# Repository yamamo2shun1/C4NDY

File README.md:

# C4NDY KeyVLM / STK

## Documentation
- [See the official documentation on https://yamamo2shun1.github.io/C4NDY/](https://yamamo2shun1.github.io/C4NDY/)

The docs are powered by [VitePress](https://vitepress.dev/). 

## Submodule
[TinyUSB](https://github.com/hathach/tinyusb) is included as a submodule in [STM32CubeIDE/C4NDY_KeyVLM](https://github.com/yamamo2shun1/C4NDY/tree/main/STM32CubeIDE/C4NDY_KeyVLM) and [STM32CubeIDE/C4NDY_STK](https://github.com/yamamo2shun1/C4NDY/tree/main/STM32CubeIDE/C4NDY_STK). Since the version of TinyUSB that we have confirmed to work is [0.17.0](https://github.com/hathach/tinyusb/releases/tag/0.17.0), please check out to the [commit](https://github.com/hathach/tinyusb/commit/5217cee5de4cd555018da90f9f1bcc87fb1c1d3a) with this tag.

## Maintainer
C4NDY is developed and maintained by Shunichi Yamamoto of Yamamoto Works Ltd.

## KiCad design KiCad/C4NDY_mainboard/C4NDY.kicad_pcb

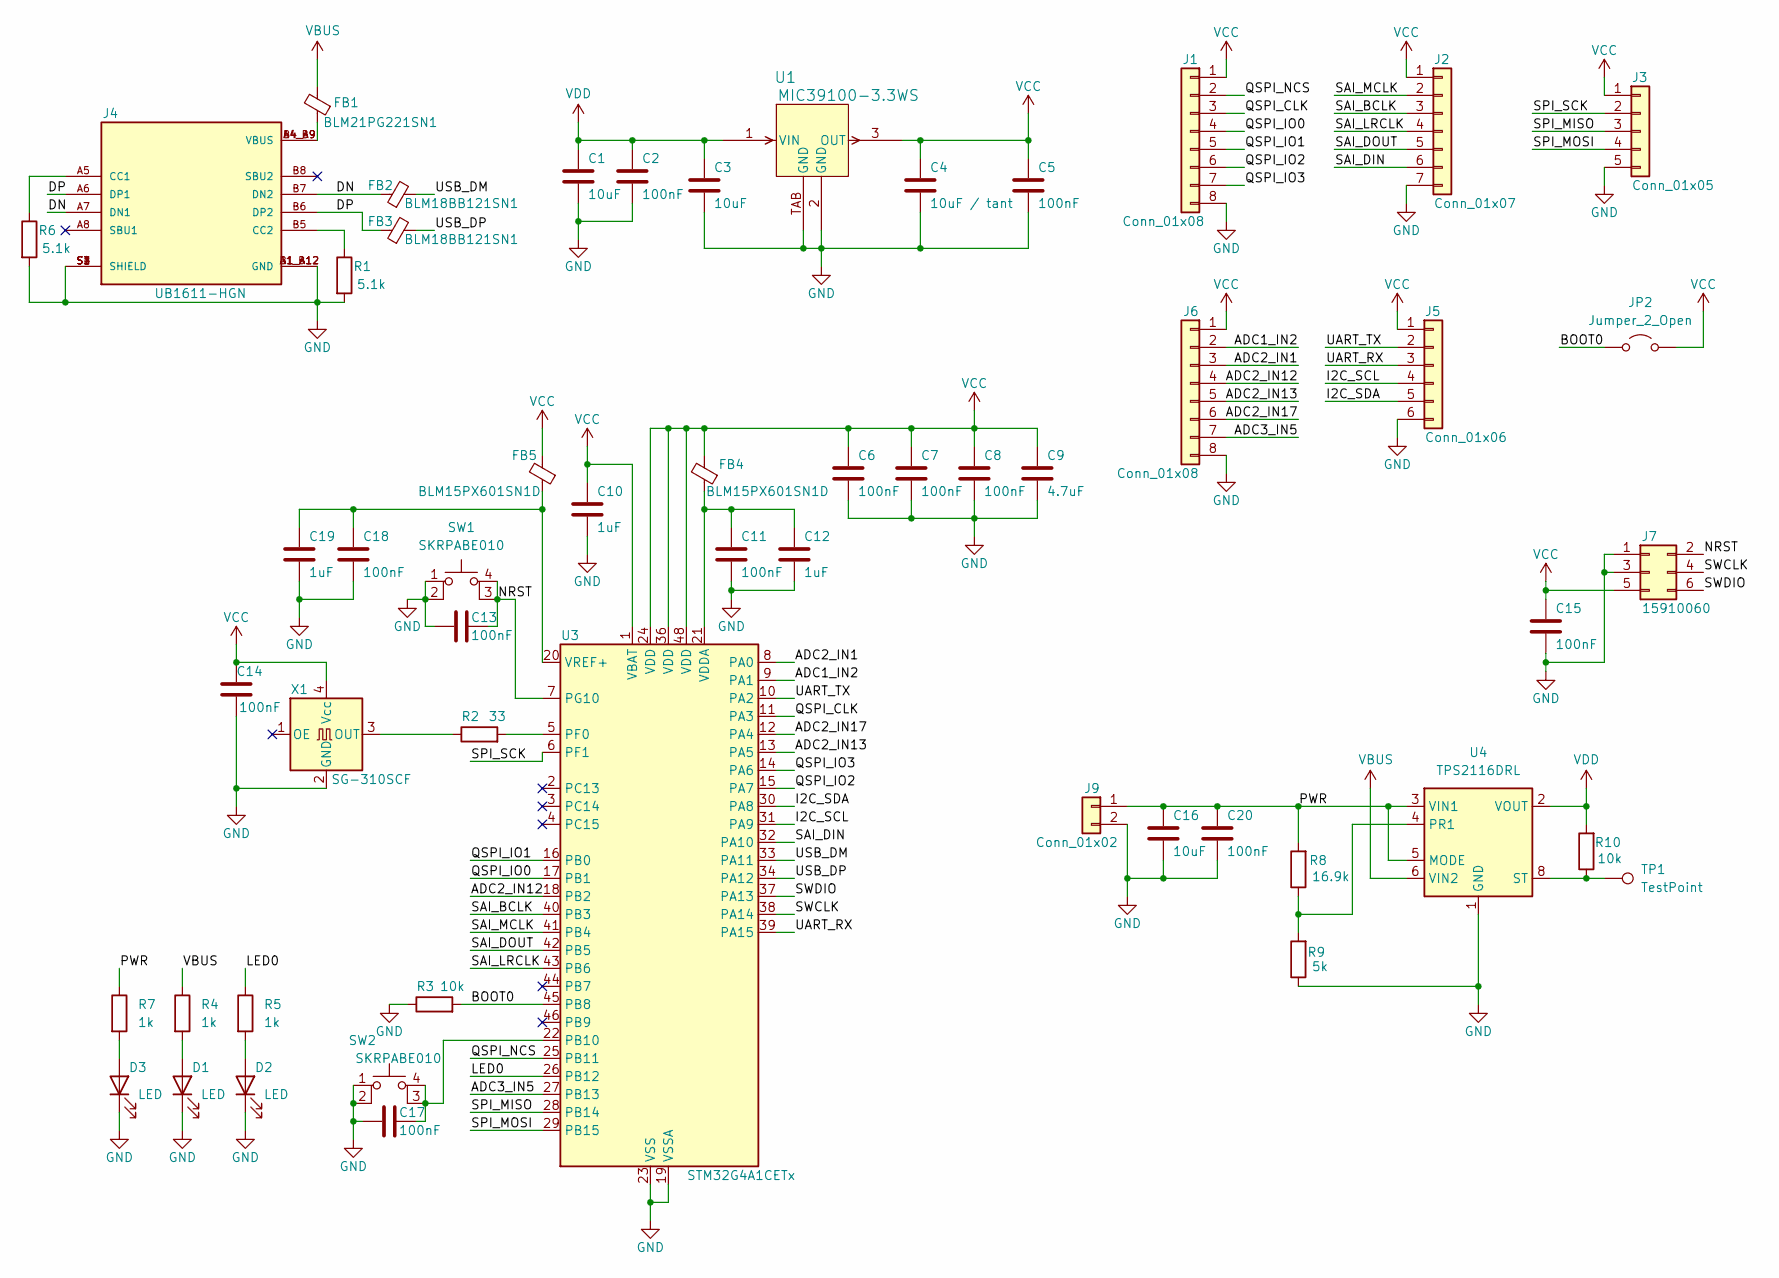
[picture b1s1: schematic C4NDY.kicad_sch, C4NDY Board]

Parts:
C1, C3, C16: 10uF; C_0603_1608Metric
C2, C5, C20: 100nF; C_0603_1608Metric
C4: 10uF / tant; CP_EIA-3528-12_Kemet-T
C6, C7, C8, C11, C13, C14, C15, C17, C18: 100nF; C_0402_1005Metric
C9: 4.7uF; C_0603_1608Metric
C10, C12, C19: 1uF; C_0402_1005Metric
D1, D2, D3: LED; LED_0603_1608Metric
FB1: BLM21PG221SN1; L_0805_2012Metric
FB2, FB3: BLM18BB121SN1; L_0603_1608Metric
FB4, FB5: BLM15PX601SN1D; L_0402_1005Metric
J1, J6: Conn_01x08; PinHeader_1x08_P2.54mm_Vertical
J2: Conn_01x07; PinHeader_1x07_P2.54mm_Vertical
J3: Conn_01x05; PinHeader_1x05_P2.54mm_Vertical
J4: UB1611-HGN; Gangyuan_UB1611-HGN; PARTREV B
J5: Conn_01x06; PinHeader_1x06_P2.54mm_Vertical
J7: 15910060; Molex_15910060
J9: Conn_01x02; PinHeader_1x02_P2.54mm_Vertical
JP2: Jumper_2_Open; SolderJumper-2_P1.3mm_Open_RoundedPad1.0x1.5mm
R1, R6: 5.1k; R_0402_1005Metric
R2: 33; R_0402_1005Metric
R3, R10: 10k; R_0402_1005Metric
R4, R5, R7: 1k; R_0402_1005Metric
R8: 16.9k; R_0402_1005Metric
R9: 5k; R_0402_1005Metric
SW1, SW2: SKRPABE010
TP1: TestPoint; TestPoint_THTPad_1.0x1.0mm_Drill0.5mm
U1: MIC39100-3.3WS; SOT-223_S_MCL
U3: STM32G4A1CETx; LQFP-48_7x7mm_P0.5mm
U4: TPS2116DRL; SOT-583-8
X1: SG-310SCF; Oscillator_SMD_SeikoEpson_SG8002CE-4Pin_3.2x2.5mm

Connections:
/ADC1_IN2: J6.2, U3.9 (PA1)
/ADC2_IN1: J6.3, U3.8 (PA0)
/ADC2_IN12: J6.4, U3.18 (PB2)
/ADC2_IN13: J6.5, U3.13 (PA5)
/ADC2_IN17: J6.6, U3.12 (PA4)
/ADC3_IN5: J6.7, U3.27 (PB13)
/BOOT0: JP2.1 (A), R3.2, U3.45 (PB8)
/DN: FB2.1, J4.A7 (DN1), J4.B7 (DN2)
/DP: FB3.1, J4.A6 (DP1), J4.B6 (DP2)
/I2C_SCL: J5.4, U3.31 (PA9)
/I2C_SDA: J5.5, U3.30 (PA8)
/LED0: R5.1, U3.26 (PB12)
/NRST: C13.1, J7.2, SW1.3 (K), SW1.4 (A), U3.7 (PG10)
/PWR: C16.1, C20.1, J9.1, R7.1, R8.2, U4.3 (VIN1), U4.5 (MODE)
/QSPI_CLK: J1.3, U3.11 (PA3)
/QSPI_IO0: J1.4, U3.17 (PB1)
/QSPI_IO1: J1.5, U3.16 (PB0)
/QSPI_IO2: J1.6, U3.15 (PA7)
/QSPI_IO3: J1.7, U3.14 (PA6)
/QSPI_NCS: J1.2, U3.25 (PB11)
/SAI_BCLK: J2.3, U3.40 (PB3)
/SAI_DIN: J2.6, U3.32 (PA10)
/SAI_DOUT: J2.5, U3.42 (PB5)
/SAI_LRCLK: J2.4, U3.43 (PB6)
/SAI_MCLK: J2.2, U3.41 (PB4)
/SPI_MISO: J3.3, U3.28 (PB14)
/SPI_MOSI: J3.4, U3.29 (PB15)
/SPI_SCK: J3.2, U3.6 (PF1)
/SWCLK: J7.4, U3.38 (PA14)
/SWDIO: J7.6, U3.37 (PA13)
/UART_RX: J5.3, U3.39 (PA15)
/UART_TX: J5.2, U3.10 (PA2)
/USB_DM: FB2.2, U3.33 (PA11)
/USB_DP: FB3.2, U3.34 (PA12)
GND: C1.2, C2.2, C3.2, C4.2, C5.2, C6.2, C7.2, C8.2, C9.2, C10.2, C11.2, C12.2, C13.2, C14.1, C15.2, C16.2, C17.2, C18.2, C19.2, C20.2, D1.1 (K), D2.1 (K), D3.1 (K), J1.8, J2.7, J3.5, J4.A1_B12 (GND), J4.B1_A12 (GND), J4.S1 (SHIELD), J4.S2 (SHIELD), J4.S3 (SHIELD), J4.S4 (SHIELD), J5.6, J6.8, J7.1, J7.3, J9.2, R1.2, R3.1, R6.2, R9.1, SW1.1, SW1.2, SW2.1, SW2.2, U1.2 (GND), U1.TAB (GND), U3.19 (VSSA), U3.23 (VSS), U3.35 (VSS), U3.47 (VSS), U4.1 (GND), X1.2 (GND)
unnamed: D1.2 (A), R4.2
unnamed: D2.2 (A), R5.2
unnamed: D3.2 (A), R7.2
unnamed: FB1.1, J4.A4_B9 (VBUS), J4.B4_A9 (VBUS)
unnamed: J4.A5 (CC1), R6.1
unnamed: J4.B5 (CC2), R1.1
unnamed: C17.1, SW2.3 (K), SW2.4 (A), U3.22 (PB10)
unnamed: R2.2, U3.5 (PF0)
unnamed: C11.1, C12.1, FB4.1, U3.21 (VDDA)
unnamed: C18.1, C19.1, FB5.1, U3.20 (VREF+)
unnamed: R8.1, R9.2, U4.4 (PR1)
unnamed: R10.1, TP1.1, U4.8 (ST)
unnamed: R2.1, X1.3 (OUT)
VBUS: FB1.2, R4.1, U4.6 (VIN2)
VCC: C4.1, C5.1, C6.1, C7.1, C8.1, C9.1, C10.1, C14.2, C15.1, FB4.2, FB5.2, J1.1, J2.1, J3.1, J5.1, J6.1, J7.5, JP2.2 (B), U1.3 (OUT), U3.1 (VBAT), U3.24 (VDD), U3.36 (VDD), U3.48 (VDD), X1.4 (Vcc)
VDD: C1.1, C2.1, C3.1, R10.2, U1.1 (VIN), U4.2 (VOUT), U4.7 (VOUT)

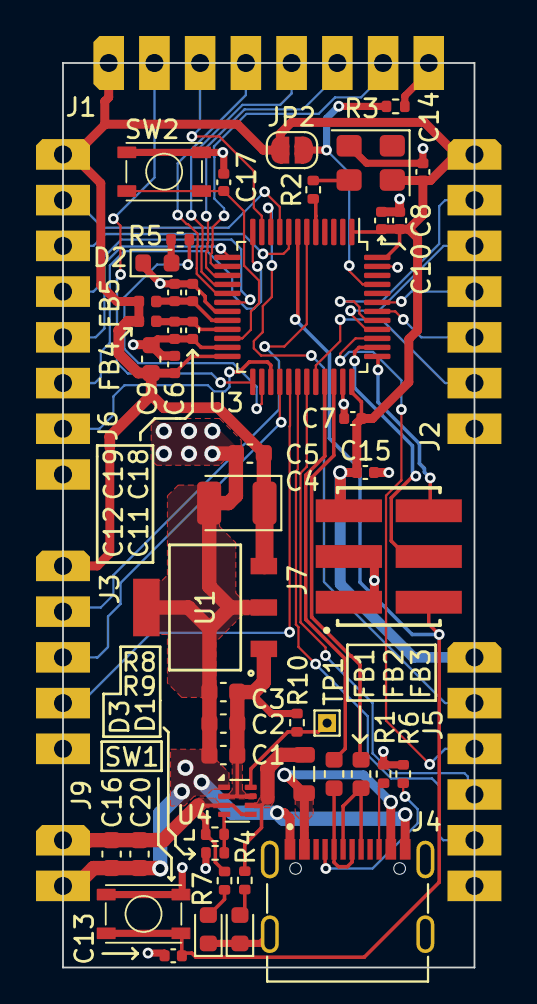
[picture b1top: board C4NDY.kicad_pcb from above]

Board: 2 copper layers, 22.9 x 50.2 mm, 54 parts (0 on the bottom side), 51 nets.

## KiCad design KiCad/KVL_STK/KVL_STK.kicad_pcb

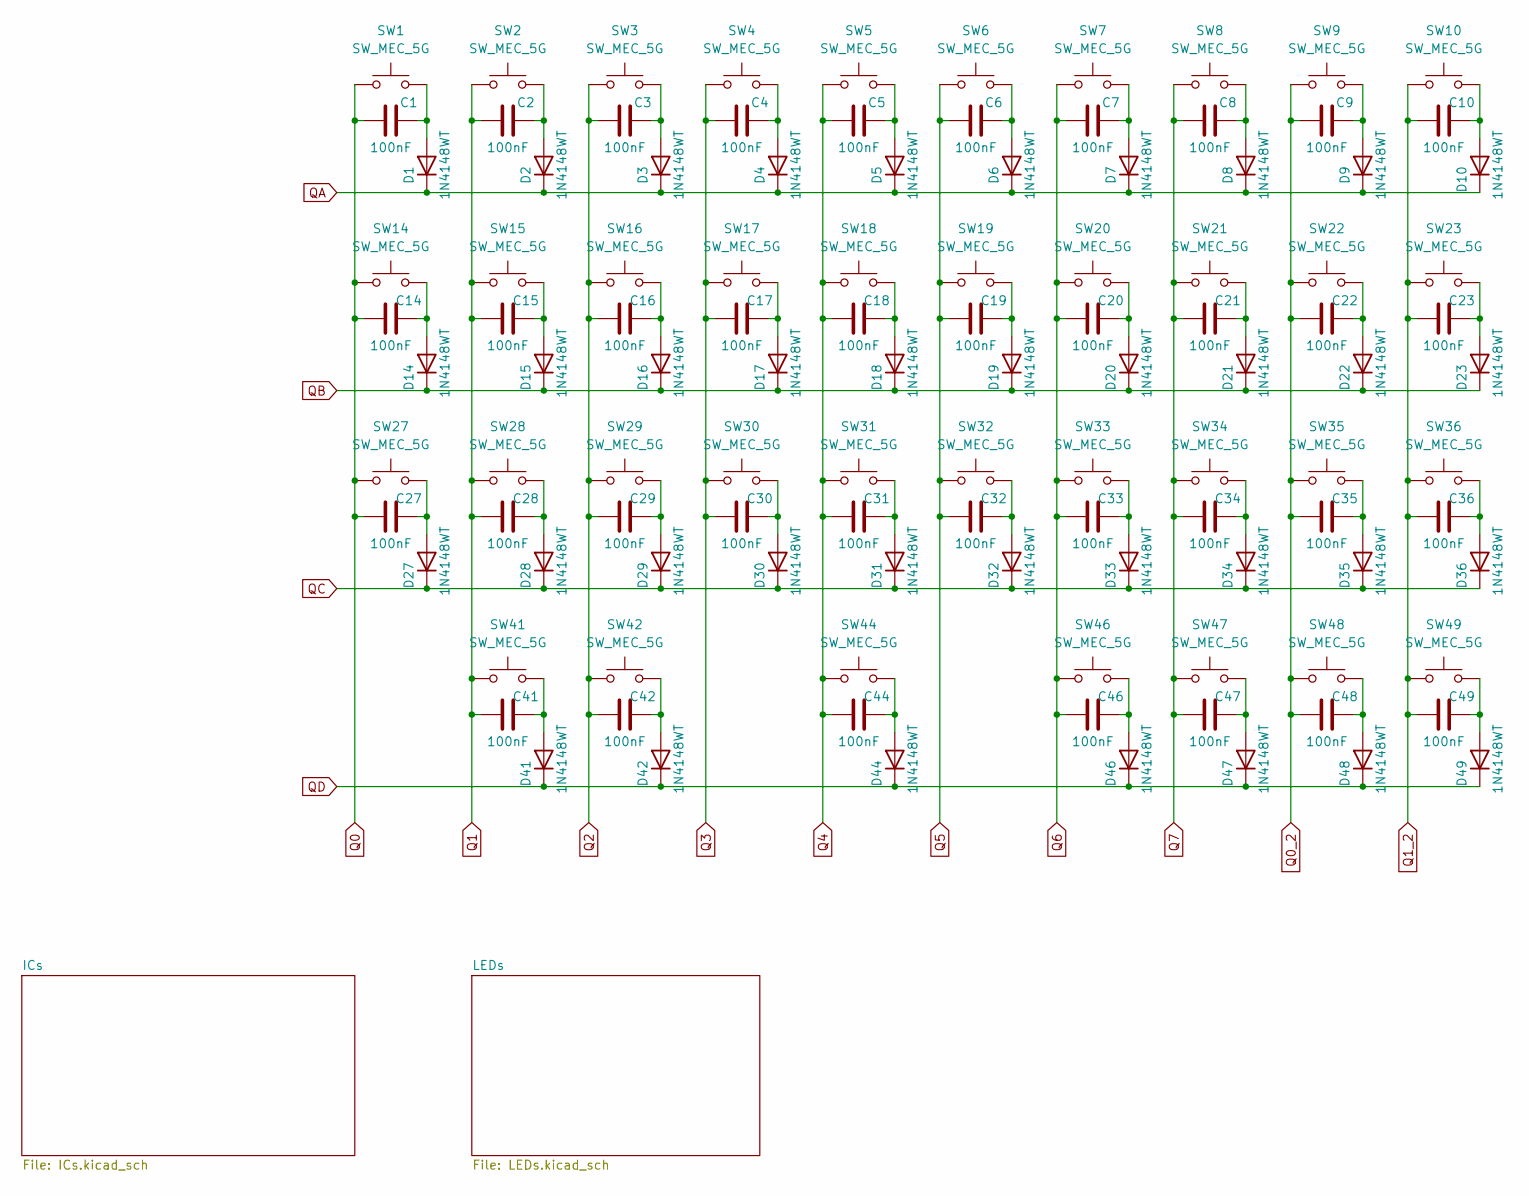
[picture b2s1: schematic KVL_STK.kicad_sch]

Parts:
C1, C2, C3, C4, C5, C6, C7, C8, C9, C10, C14, C15, C16, C17, C18, C19, C20, C21, C22, C23, C27, C28, C29, C30, C31, C32, C33, C34, C35, C36, C41, C42, C44, C46, C47, C48, C49: 100nF; C_0402_1005Metric
D1, D2, D3, D4, D5, D6, D7, D8, D9, D10, D14, D15, D16, D17, D18, D19, D20, D21, D22, D23, D27, D28, D29, D30, D31, D32, D33, D34, D35, D36, D41, D42, D44, D46, D47, D48, D49: 1N4148WT; D_SOD-523
SW1, SW2, SW3, SW4, SW5, SW6, SW7, SW8, SW9, SW10, SW14, SW15, SW16, SW17, SW18, SW19, SW20, SW21, SW22, SW23, SW27, SW28, SW29, SW30, SW31, SW32, SW33, SW34, SW35, SW36, SW41, SW42, SW44, SW46, SW47, SW48, SW49: SW_MEC_5G; Gateron_KS-27

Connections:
unnamed: C1.2, D1.2 (A), SW1.3 (B)
unnamed: C3.2, D3.2 (A), SW3.3 (B)
unnamed: C4.2, D4.2 (A), SW4.3 (B)
unnamed: C5.2, D5.2 (A), SW5.3 (B)
unnamed: C6.2, D6.2 (A), SW6.3 (B)
unnamed: C7.2, D7.2 (A), SW7.3 (B)
unnamed: C8.2, D8.2 (A), SW8.3 (B)
unnamed: C9.2, D9.2 (A), SW9.3 (B)
unnamed: C10.2, D10.2 (A), SW10.3 (B)
unnamed: C14.2, D14.2 (A), SW14.3 (B)
unnamed: C15.2, D15.2 (A), SW15.3 (B)
unnamed: C16.2, D16.2 (A), SW16.3 (B)
unnamed: C17.2, D17.2 (A), SW17.3 (B)
unnamed: C18.2, D18.2 (A), SW18.3 (B)
unnamed: C19.2, D19.2 (A), SW19.3 (B)
unnamed: C20.2, D20.2 (A), SW20.3 (B)
unnamed: C21.2, D21.2 (A), SW21.3 (B)
unnamed: C22.2, D22.2 (A), SW22.3 (B)
unnamed: C23.2, D23.2 (A), SW23.3 (B)
unnamed: C27.2, D27.2 (A), SW27.3 (B)
unnamed: C28.2, D28.2 (A), SW28.3 (B)
unnamed: C29.2, D29.2 (A), SW29.3 (B)
unnamed: C30.2, D30.2 (A), SW30.3 (B)
unnamed: C31.2, D31.2 (A), SW31.3 (B)
unnamed: C32.2, D32.2 (A), SW32.3 (B)
unnamed: C33.2, D33.2 (A), SW33.3 (B)
unnamed: C34.2, D34.2 (A), SW34.3 (B)
unnamed: C35.2, D35.2 (A), SW35.3 (B)
unnamed: C36.2, D36.2 (A), SW36.3 (B)
unnamed: C41.2, D41.2 (A), SW41.3 (B)
unnamed: C42.2, D42.2 (A), SW42.3 (B)
unnamed: C44.2, D44.2 (A), SW44.3 (B)
unnamed: C46.2, D46.2 (A), SW46.3 (B)
unnamed: C47.2, D47.2 (A), SW47.3 (B)
unnamed: C48.2, D48.2 (A), SW48.3 (B)
unnamed: C49.2, D49.2 (A), SW49.3 (B)
Q0: C1.1, C14.1, C27.1, SW1.1 (A), SW14.1 (A), SW27.1 (A); also elsewhere on the board
Q0_2: C9.1, C22.1, C35.1, C48.1, SW9.1 (A), SW22.1 (A), SW35.1 (A), SW48.1 (A); also elsewhere on the board
Q1: C2.1, C15.1, C28.1, C41.1, SW2.1 (A), SW15.1 (A), SW28.1 (A), SW41.1 (A); also elsewhere on the board
Q1_2: C10.1, C23.1, C36.1, C49.1, SW10.1 (A), SW23.1 (A), SW36.1 (A), SW49.1 (A); also elsewhere on the board
Q2: C3.1, C16.1, C29.1, C42.1, SW3.1 (A), SW16.1 (A), SW29.1 (A), SW42.1 (A); also elsewhere on the board
Q3: C4.1, C17.1, C30.1, SW4.1 (A), SW17.1 (A), SW30.1 (A); also elsewhere on the board
Q4: C5.1, C18.1, C31.1, C44.1, SW5.1 (A), SW18.1 (A), SW31.1 (A), SW44.1 (A); also elsewhere on the board
Q5: C6.1, C19.1, C32.1, SW6.1 (A), SW19.1 (A), SW32.1 (A); also elsewhere on the board
Q6: C7.1, C20.1, C33.1, C46.1, SW7.1 (A), SW20.1 (A), SW33.1 (A), SW46.1 (A); also elsewhere on the board
Q7: C8.1, C21.1, C34.1, C47.1, SW8.1 (A), SW21.1 (A), SW34.1 (A), SW47.1 (A); also elsewhere on the board
QB: D14.1 (K), D15.1 (K), D16.1 (K), D17.1 (K), D18.1 (K), D19.1 (K), D20.1 (K), D21.1 (K), D22.1 (K), D23.1 (K); also elsewhere on the board
QC: D27.1 (K), D28.1 (K), D29.1 (K), D30.1 (K), D31.1 (K), D32.1 (K), D33.1 (K), D34.1 (K), D35.1 (K), D36.1 (K); also elsewhere on the board
QD: D41.1 (K), D42.1 (K), D44.1 (K), D46.1 (K), D47.1 (K), D48.1 (K), D49.1 (K); also elsewhere on the board

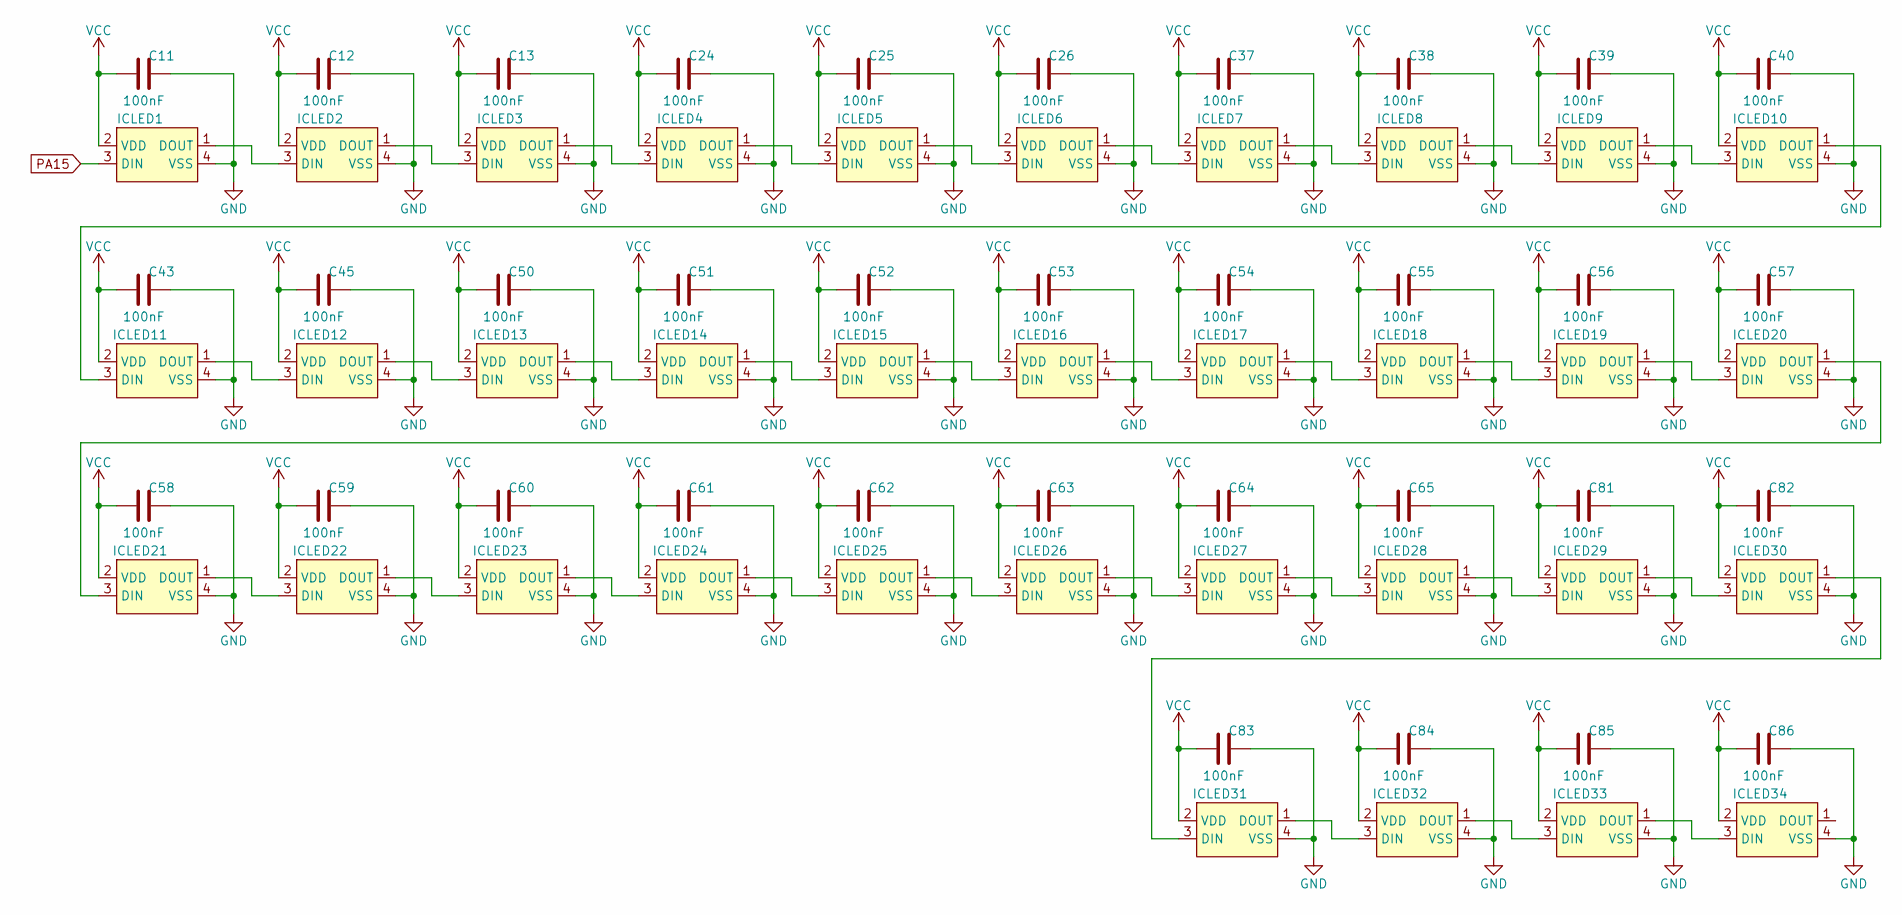
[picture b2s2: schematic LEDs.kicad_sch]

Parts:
C11, C12, C13, C24, C25, C26, C37, C38, C39, C40, C43, C45, C50, C51, C52, C53, C54, C55, C56, C57, C58, C59, C60, C61, C62, C63, C64, C65, C81, C82, C83, C84, C85, C86: 100nF; C_0402_1005Metric
ICLED1, ICLED2, ICLED3, ICLED4, ICLED5, ICLED6, ICLED7, ICLED8, ICLED9, ICLED10, ICLED11, ICLED12, ICLED13, ICLED14, ICLED15, ICLED16, ICLED17, ICLED18, ICLED19, ICLED20, ICLED21, ICLED22, ICLED23, ICLED24, ICLED25, ICLED26, ICLED27, ICLED28, ICLED29, ICLED30, ICLED31, ICLED32, ICLED33, ICLED34: 1312020030000

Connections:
unnamed: ICLED1.1 (DOUT), ICLED2.3 (DIN)
unnamed: ICLED2.1 (DOUT), ICLED3.3 (DIN)
unnamed: ICLED3.1 (DOUT), ICLED4.3 (DIN)
unnamed: ICLED4.1 (DOUT), ICLED5.3 (DIN)
unnamed: ICLED5.1 (DOUT), ICLED6.3 (DIN)
unnamed: ICLED6.1 (DOUT), ICLED7.3 (DIN)
unnamed: ICLED7.1 (DOUT), ICLED8.3 (DIN)
unnamed: ICLED8.1 (DOUT), ICLED9.3 (DIN)
unnamed: ICLED9.1 (DOUT), ICLED10.3 (DIN)
unnamed: ICLED10.1 (DOUT), ICLED11.3 (DIN)
unnamed: ICLED11.1 (DOUT), ICLED12.3 (DIN)
unnamed: ICLED12.1 (DOUT), ICLED13.3 (DIN)
unnamed: ICLED13.1 (DOUT), ICLED14.3 (DIN)
unnamed: ICLED14.1 (DOUT), ICLED15.3 (DIN)
unnamed: ICLED15.1 (DOUT), ICLED16.3 (DIN)
unnamed: ICLED16.1 (DOUT), ICLED17.3 (DIN)
unnamed: ICLED17.1 (DOUT), ICLED18.3 (DIN)
unnamed: ICLED18.1 (DOUT), ICLED19.3 (DIN)
unnamed: ICLED19.1 (DOUT), ICLED20.3 (DIN)
unnamed: ICLED20.1 (DOUT), ICLED21.3 (DIN)
unnamed: ICLED21.1 (DOUT), ICLED22.3 (DIN)
unnamed: ICLED22.1 (DOUT), ICLED23.3 (DIN)
unnamed: ICLED23.1 (DOUT), ICLED24.3 (DIN)
unnamed: ICLED24.1 (DOUT), ICLED25.3 (DIN)
unnamed: ICLED25.1 (DOUT), ICLED26.3 (DIN)
unnamed: ICLED26.1 (DOUT), ICLED27.3 (DIN)
unnamed: ICLED27.1 (DOUT), ICLED28.3 (DIN)
unnamed: ICLED28.1 (DOUT), ICLED29.3 (DIN)
unnamed: ICLED29.1 (DOUT), ICLED30.3 (DIN)
unnamed: ICLED30.1 (DOUT), ICLED31.3 (DIN)
unnamed: ICLED31.1 (DOUT), ICLED32.3 (DIN)
unnamed: ICLED32.1 (DOUT), ICLED33.3 (DIN)
unnamed: ICLED33.1 (DOUT), ICLED34.3 (DIN)
PA15: ICLED1.3 (DIN); also elsewhere on the board
VCC: C11.1, C12.1, C13.1, C24.1, C25.1, C26.1, C37.1, C38.1, C39.1, C40.1, C43.1, C45.1, C50.1, C51.1, C52.1, C53.1, C54.1, C55.1, C56.1, C57.1, C58.1, C59.1, C60.1, C61.1, C62.1, C63.1, C64.1, C65.1, C81.1, C82.1, C83.1, C84.1, C85.1, C86.1, ICLED1.2 (VDD), ICLED2.2 (VDD), ICLED3.2 (VDD), ICLED4.2 (VDD), ICLED5.2 (VDD), ICLED6.2 (VDD), ICLED7.2 (VDD), ICLED8.2 (VDD), ICLED9.2 (VDD), ICLED10.2 (VDD), ICLED11.2 (VDD), ICLED12.2 (VDD), ICLED13.2 (VDD), ICLED14.2 (VDD), ICLED15.2 (VDD), ICLED16.2 (VDD), ICLED17.2 (VDD), ICLED18.2 (VDD), ICLED19.2 (VDD), ICLED20.2 (VDD), ICLED21.2 (VDD), ICLED22.2 (VDD), ICLED23.2 (VDD), ICLED24.2 (VDD), ICLED25.2 (VDD), ICLED26.2 (VDD), ICLED27.2 (VDD), ICLED28.2 (VDD), ICLED29.2 (VDD), ICLED30.2 (VDD), ICLED31.2 (VDD), ICLED32.2 (VDD), ICLED33.2 (VDD), ICLED34.2 (VDD); also elsewhere on the board

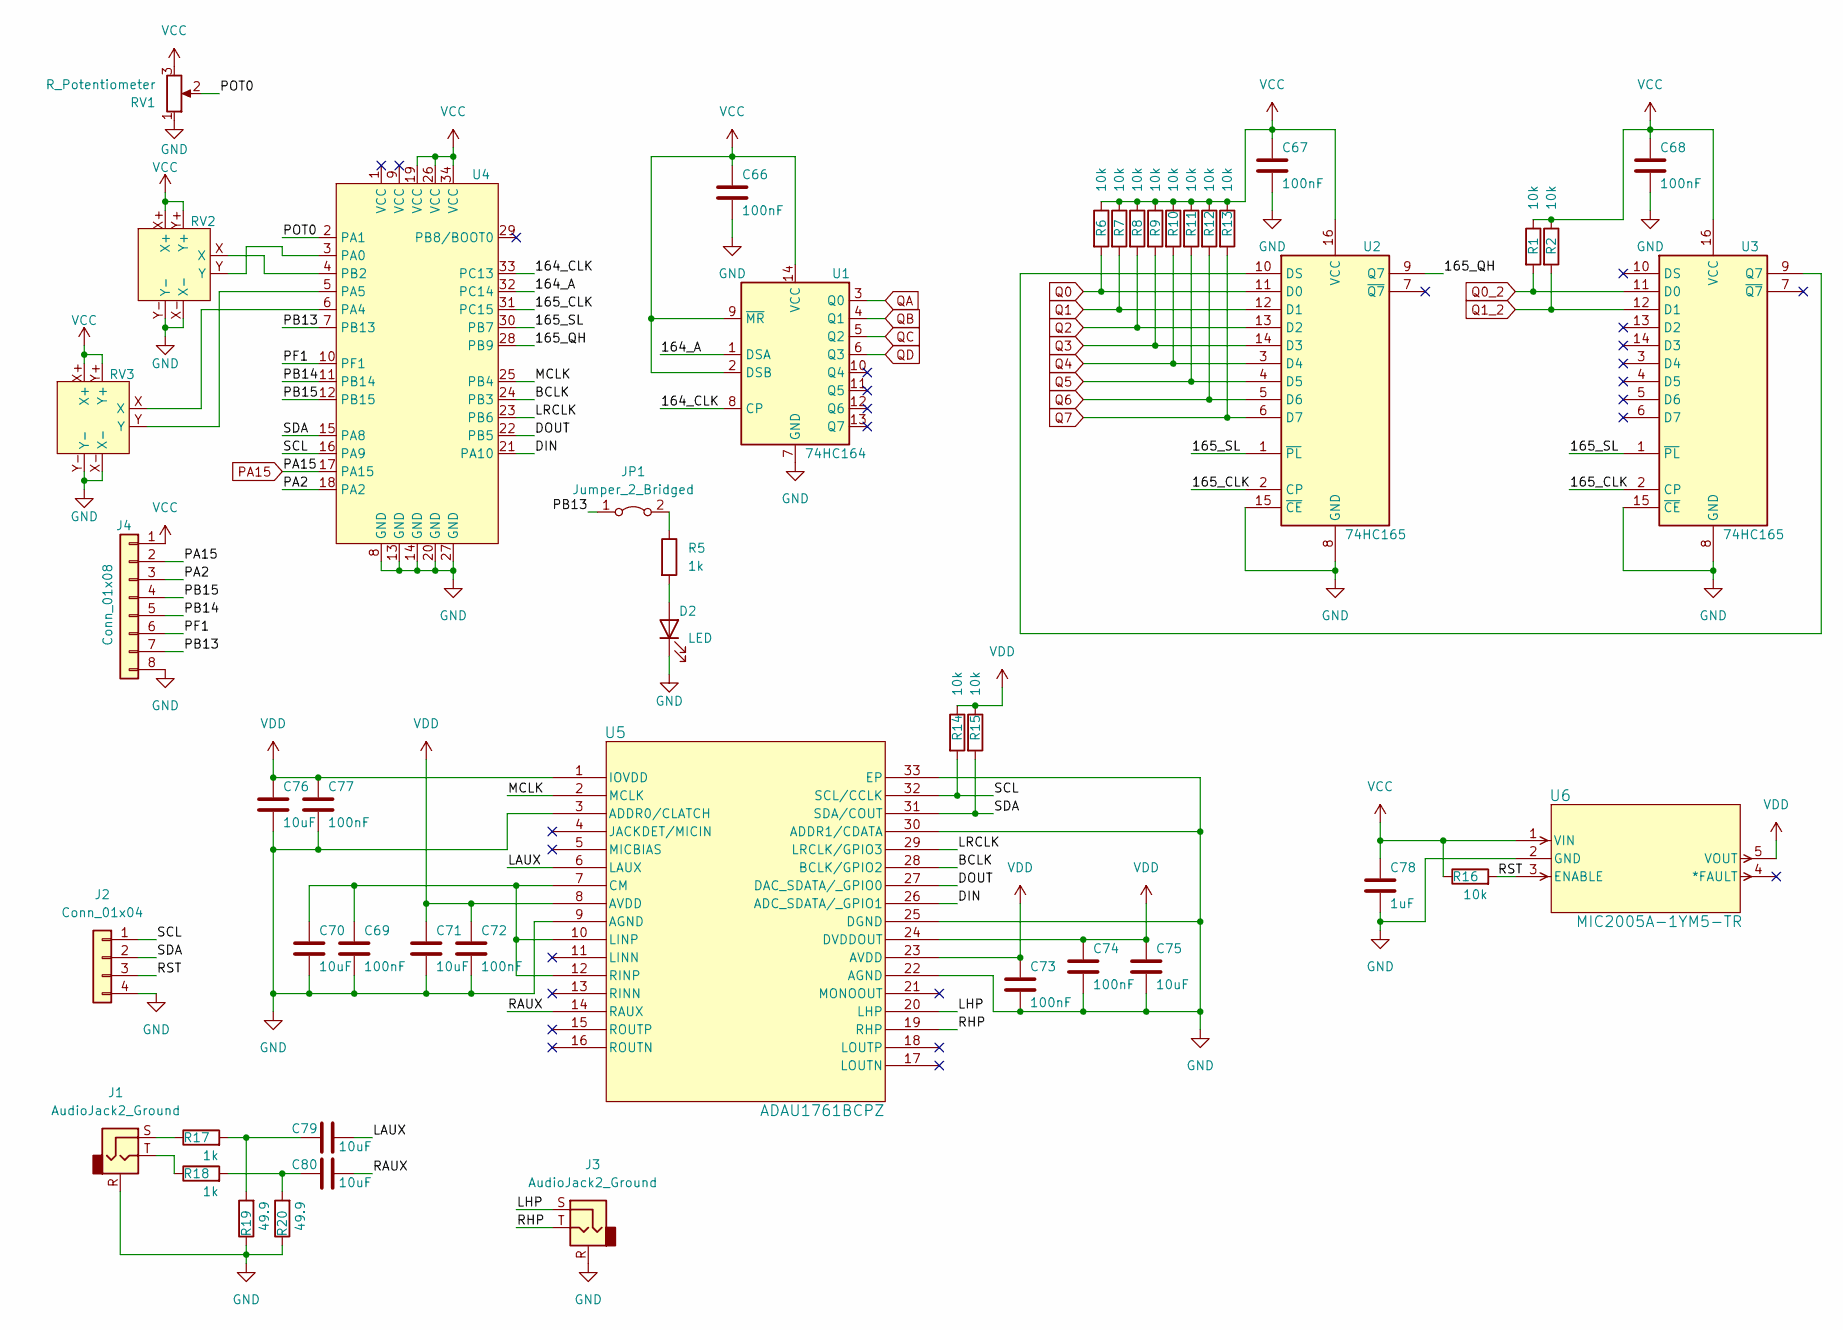
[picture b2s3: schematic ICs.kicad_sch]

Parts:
C66, C67, C68, C69, C72, C73, C74, C77: 100nF; C_0402_1005Metric
C70, C71, C75, C76, C79, C80: 10uF; C_0603_1608Metric
C78: 1uF; C_0603_1608Metric
D2: LED; LED_0603_1608Metric
J1, J3: AudioJack2_Ground; Jack_3.5mm_QingPu_WQP-PJ366ST_Vertical
J2: Conn_01x04; PinHeader_1x04_P2.54mm_Vertical
J4: Conn_01x08; PinHeader_1x08_P2.54mm_Vertical
JP1: Jumper_2_Bridged; SolderJumper-2_P1.3mm_Bridged_RoundedPad1.0x1.5mm
R1, R2, R6, R7, R8, R9, R10, R11, R12, R13, R14, R15, R16: 10k; R_0402_1005Metric
R5, R17, R18: 1k; R_0402_1005Metric
R19, R20: 49.9; R_0402_1005Metric
RV1: R_Potentiometer; RK09K1130A5R
RV2, RV3: ADA-2765
U1: 74HC164; SOIC-14_3.9x8.7mm_P1.27mm
U2, U3: 74HC165; SOIC-16_3.9x9.9mm_P1.27mm
U4: C4NDY_BOARD
U5: ADAU1761BCPZ; CP_32_4_ADI
U6: MIC2005A-1YM5-TR; SOT-23-5_M5_MCH

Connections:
/ICs/164_A: U1.1 (DSA), U4.32 (PC14)
/ICs/164_CLK: U1.8 (CP), U4.33 (PC13)
/ICs/165_CLK: U2.2 (CP), U3.2 (CP), U4.31 (PC15)
/ICs/165_QH: U2.9 (Q7), U4.28 (PB9)
/ICs/165_SL: U2.1 (~PL), U3.1 (~PL), U4.30 (PB7)
/ICs/BCLK: U4.24 (PB3), U5.28 (BCLK/GPIO2)
/ICs/DIN: U4.21 (PA10), U5.26 (ADC_SDATA/_GPIO1)
/ICs/DOUT: U4.22 (PB5), U5.27 (DAC_SDATA/_GPIO0)
/ICs/LAUX: C79.2, U5.6 (LAUX)
/ICs/LHP: J3.S, U5.20 (LHP)
/ICs/LRCLK: U4.23 (PB6), U5.29 (LRCLK/GPIO3)
/ICs/MCLK: U4.25 (PB4), U5.2 (MCLK)
/ICs/PA2: J4.3, U4.18 (PA2)
/ICs/PB13: J4.7, JP1.1 (A), U4.7 (PB13)
/ICs/PB14: J4.5, U4.11 (PB14)
/ICs/PB15: J4.4, U4.12 (PB15)
/ICs/PF1: J4.6, U4.10 (PF1)
/ICs/POT0: RV1.2, U4.2 (PA1)
/ICs/RAUX: C80.2, U5.14 (RAUX)
/ICs/RHP: J3.T, U5.19 (RHP)
/ICs/RST: J2.3, R16.2, U6.3 (ENABLE)
/ICs/SCL: J2.1, R14.2, U4.16 (PA9), U5.32 (SCL/CCLK)
/ICs/SDA: J2.2, R15.2, U4.15 (PA8), U5.31 (SDA/COUT)
unnamed: C79.1, R17.2, R19.2
unnamed: C80.1, R18.2, R20.2
unnamed: J1.S, R17.1
unnamed: J1.T, R18.1
unnamed 96: JP1.2 (B); also elsewhere on the board
unnamed: U2.10 (DS), U3.9 (Q7)
unnamed: RV2.Y, U4.3 (PA0)
unnamed: RV3.X, U4.6 (PA4)
unnamed: RV3.Y, U4.5 (PA5)
unnamed: RV2.X, U4.4 (PB2)
unnamed: C69.1, C70.1, U5.7 (CM), U5.10 (LINP), U5.12 (RINP)
PA15: J4.2, U4.17 (PA15); also elsewhere on the board
Q0: R6.2, U2.11 (D0); also elsewhere on the board
Q0_2: R1.2, U3.11 (D0); also elsewhere on the board
Q1: R7.2, U2.12 (D1); also elsewhere on the board
Q1_2: R2.2, U3.12 (D1); also elsewhere on the board
Q2: R8.2, U2.13 (D2); also elsewhere on the board
Q3: R9.2, U2.14 (D3); also elsewhere on the board
Q4: R10.2, U2.3 (D4); also elsewhere on the board
Q5: R11.2, U2.4 (D5); also elsewhere on the board
Q6: R12.2, U2.5 (D6); also elsewhere on the board
Q7: R13.2, U2.6 (D7); also elsewhere on the board
QB: U1.4 (Q1); also elsewhere on the board
QC: U1.5 (Q2); also elsewhere on the board
QD: U1.6 (Q3); also elsewhere on the board
VCC: C66.1, C67.1, C68.1, C78.1, J4.1, R1.1, R2.1, R6.1, R7.1, R8.1, R9.1, R10.1, R11.1, R12.1, R13.1, R16.1, RV1.3, RV2.X+, RV2.Y+, RV3.X+, RV3.Y+, U1.2 (DSB), U1.9 (~MR), U1.14 (VCC), U2.16 (VCC), U3.16 (VCC), U4.19 (VCC), U4.26 (VCC), U4.34 (VCC), U6.1 (VIN); also elsewhere on the board
VDD: C71.1, C72.1, C73.1, C74.1, C75.1, C76.1, C77.1, R14.1, R15.1, U5.1 (IOVDD), U5.8 (AVDD), U5.23 (AVDD), U5.24 (DVDDOUT), U6.5 (VOUT)

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
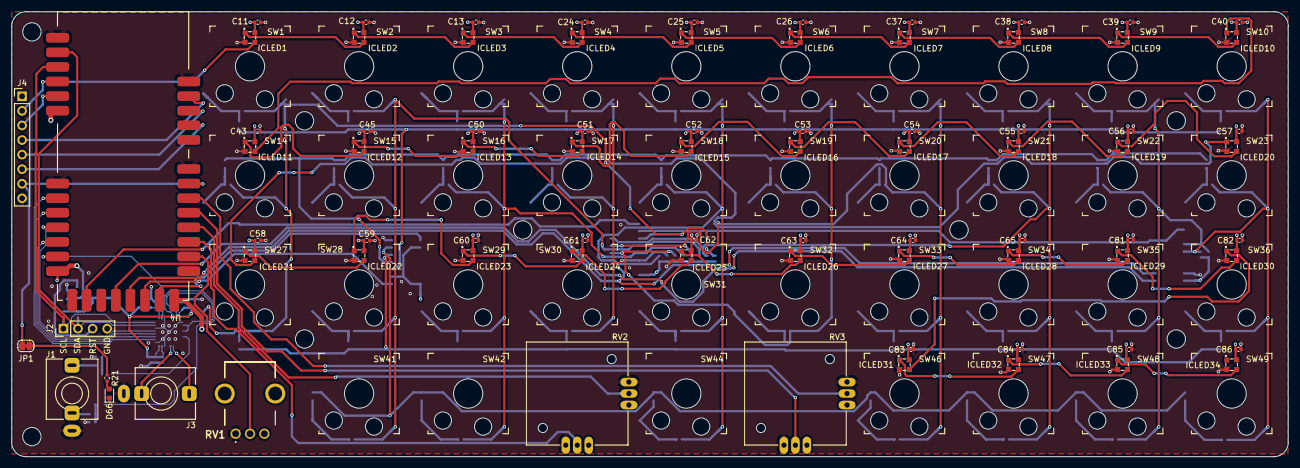
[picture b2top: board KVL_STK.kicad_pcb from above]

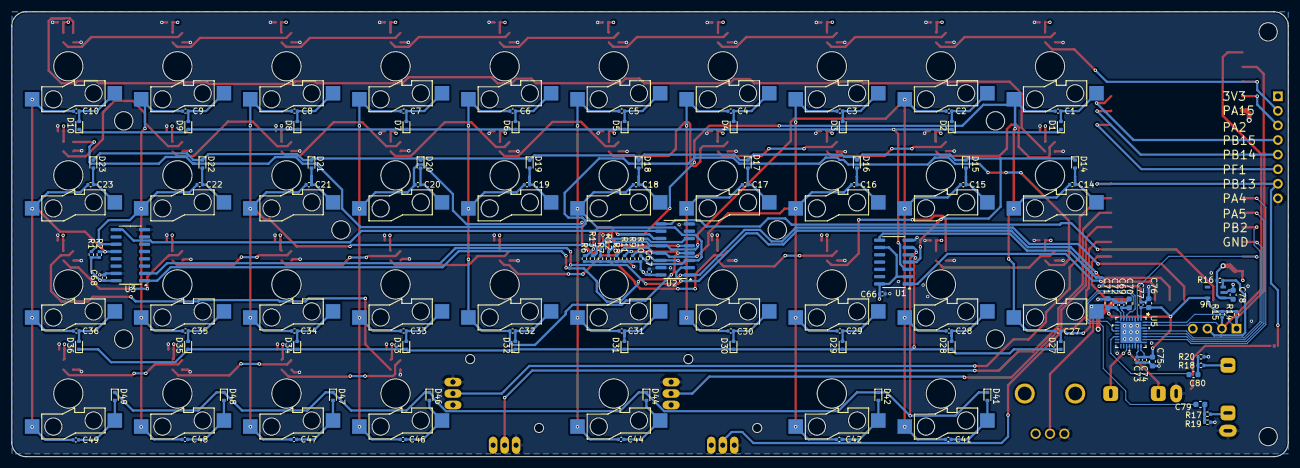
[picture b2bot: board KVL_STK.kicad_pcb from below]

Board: 4 copper layers, 222.3 x 77.5 mm, 235 parts (148 on the bottom side), 123 nets.

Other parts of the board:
D66: LED; LED_0603_1608Metric
MH1, MH2, MH4, MH4#2, MH5, MH6, MH7, MH8: MountingHole_3.2mm_M3
R21: 1k; R_0402_1005Metric

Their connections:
unnamed 96: R21.1; also elsewhere on the board

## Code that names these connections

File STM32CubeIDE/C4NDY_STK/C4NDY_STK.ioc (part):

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Mcu.Name=STM32G491C(C-E)Tx
Mcu.Package=LQFP48
Mcu.UserName=STM32G491CETx
PA0.Signal=SharedAnalog_PA0
PA1.Signal=SharedAnalog_PA1
PA11.Mode=Device
PA11.Signal=USB_DM
PA12.Mode=Device
PA12.Signal=USB_DP
PA13.Mode=Serial_Wire
PA13.Signal=SYS_JTMS-SWDIO
PA14.Mode=Serial_Wire
PA14.Signal=SYS_JTCK-SWCLK
PA15.Signal=S_TIM8_CH1
PA3.GPIOParameters=GPIO_Speed
PA3.GPIO_Speed=GPIO_SPEED_FREQ_VERY_HIGH
PA3.Mode=Single Bank 1
PA3.Signal=QUADSPI1_CLK
PA4.Signal=SharedAnalog_PA4
PA5.Signal=SharedAnalog_PA5
PA6.GPIOParameters=GPIO_Speed
PA6.GPIO_Speed=GPIO_SPEED_FREQ_VERY_HIGH
PA6.Mode=Single Bank 1
PA6.Signal=QUADSPI1_BK1_IO3
PA7.GPIOParameters=GPIO_Speed
PA7.GPIO_Speed=GPIO_SPEED_FREQ_VERY_HIGH
PA7.Mode=Single Bank 1
PA7.Signal=QUADSPI1_BK1_IO2
PA8.Mode=I2C
PA8.Signal=I2C2_SDA
PA9.Mode=I2C
PA9.Signal=I2C2_SCL
PB0.GPIOParameters=GPIO_Speed
PB0.GPIO_Speed=GPIO_SPEED_FREQ_VERY_HIGH
PB0.Mode=Single Bank 1
PB0.Signal=QUADSPI1_BK1_IO1
PB1.GPIOParameters=GPIO_Speed
PB1.GPIO_Speed=GPIO_SPEED_FREQ_VERY_HIGH
PB1.Mode=Single Bank 1
PB1.Signal=QUADSPI1_BK1_IO0
PB10.GPIOParameters=GPIO_PuPd,GPIO_Label
PB10.GPIO_Label=USER_SW
PB10.GPIO_PuPd=GPIO_PULLUP
PB10.Signal=GPIO_Input
PB11.GPIOParameters=GPIO_Speed
PB11.GPIO_Speed=GPIO_SPEED_FREQ_VERY_HIGH
PB11.Mode=Single Bank 1
PB11.Signal=QUADSPI1_BK1_NCS
PB12.GPIOParameters=GPIO_Label
PB12.GPIO_Label=USER_LED
PB12.Signal=GPIO_Output
PB13.GPIOParameters=GPIO_Label
PB13.GPIO_Label=LP_LED
PB13.Signal=GPIO_Output
PB2.Signal=SharedAnalog_PB2
PB3.GPIOParameters=GPIO_Speed
PB3.GPIO_Speed=GPIO_SPEED_FREQ_VERY_HIGH
PB3.Mode=SAI_B_MasterWithClock
PB3.Signal=SAI1_SCK_B
PB4.GPIOParameters=GPIO_Speed
PB4.GPIO_Speed=GPIO_SPEED_FREQ_VERY_HIGH
PB4.Mode=SAI_B_MasterWithClock
PB4.Signal=SAI1_MCLK_B
PB5.GPIOParameters=GPIO_Speed
PB5.GPIO_Speed=GPIO_SPEED_FREQ_VERY_HIGH
PB5.Mode=SAI_B_MasterWithClock
PB5.Signal=SAI1_SD_B
PB6.GPIOParameters=GPIO_Speed,GPIO_FM6
PB6.GPIO_FM6=__NULL
PB6.GPIO_Speed=GPIO_SPEED_FREQ_VERY_HIGH
PB6.Mode=SAI_B_MasterWithClock
PB6.Signal=SAI1_FS_B
PB7.GPIOParameters=GPIO_Speed,GPIO_Label
PB7.GPIO_Label=HC165_SL
PB7.GPIO_Speed=GPIO_SPEED_FREQ_HIGH
PB7.Signal=GPIO_Output
PB9.GPIOParameters=GPIO_Label
PB9.GPIO_Label=HC165_QH
PB9.Signal=GPIO_Input
PC13.GPIOParameters=GPIO_Label
PC13.GPIO_Label=HC164_CLK
PC13.Signal=GPIO_Output
PC14-OSC32_IN.GPIOParameters=GPIO_Label
PC14-OSC32_IN.GPIO_Label=HC164_A
PC14-OSC32_IN.Signal=GPIO_Output
PC15-OSC32_OUT.GPIOParameters=GPIO_Label
PC15-OSC32_OUT.GPIO_Label=HC165_CLK
PC15-OSC32_OUT.Signal=GPIO_Output
PF0-OSC_IN.Mode=HSE-External-Clock-Source
PF0-OSC_IN.Signal=RCC_OSC_IN
RCC.HSE_VALUE=12288000
RCC.SYSCLKFreq_VALUE=147456000
RCC.SYSCLKSource=RCC_SYSCLKSOURCE_PLLCLK
board=custom
